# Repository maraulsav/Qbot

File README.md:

# Qbot-the-self-balancing-robot
Qbot is a self balancing robot that integrate PID mechanism to balances.

The Final Design:

## Key Features
* **ESP32 DevKit C** is the main microcontroller allowing wifi connection for remote controller
* **OLED display 128 x 64 px** for displaying the faces and current state of emotion
* **15 V Lipo Battery** to give power supply
* **MPU 6050** Act as gyroscope and accelerator to measure the degree of robot imbalance
* **Buzzer** to make sounds
* **Button** to regulate the power supply from battery
* **DC DC Buck Converter** to regulate the voltage supply
* **TMC2208 Motor Driver** To help control the wheel motion

## Printed Circuit Board (PCB)
Below is the schematic that I used

Below is the PCB design

And here how to connect the PCB to other component of the robot

**PCB Footprint List**
* 10uF capacitor: Capacitor_THT:CP_Radial_D5.0mm_P2.00mm
* 100uF capacitor: Capacitor_THT:CP_Radial_D6.3mm_P2.50mm
* Zener Diode: Diode_THT:D_DO-35_SOD27_P10.16mm_Horizontal
* LED: LED_THT:LED_D3.0mm
* Mounting Hole: MountingHole:MountingHole_3.2mm_M3
* Connector: Connector_PinHeader_2.54mm:PinHeader_1x04_P2.54mm_Vertical
* Connector 1x02: Connector_AMASS:AMASS_XT30U-M_1x02_P5.0mm_Vertical
* GY521 (MPU6050): GY-521:MODULE_GY-521
* ESP32 DevKit C: Library:MODULE_ESP32-DEVKITC
* TMC2208_SILENTSTEPSTICK:MODULE_TMC2208_SILENTSTEPSTICK

## 3D Design
Note that I would be using 12 cm wheel

Front Side

Right Side

Back Side

## Codes
Code Sample:

## BOM
| Component | Qty | Total (IDR) | Total (USD) | Link |
|-----------|----:|------------:|------------:|------|
| Stepper Motor 17HS4401S | 2 | - | $19.08 |[Link](https://www.aliexpress.com/item/1005008098470320.html?spm=a2g0o.productlist.main.2.28cfa8cpa8cpOK&algo_pvid=d640442b-15d3-4dfb-b6e0-f32e19ed61e5&algo_exp_id=d640442b-15d3-4dfb-b6e0-f32e19ed61e5-1&pdp_ext_f=%7B%22order%22%3A%2252%22%2C%22spu_best_type%22%3A%22price%22%2C%22eval%22%3A%221%22%2C%22fromPage%22%3A%22search%22%7D&pdp_npi=6%40dis%21SGD%219.54%215.26%21%21%217.26%214.00%21%400be71e1e17897422834053183e0cf3%2112000043729379107%21sea%21SG%210%21ABX%211%210%21n_tag%3A-29910%3Bd%3A420eb142%3Bm03_new_user%3A-29895%3BpisId%3A5000000216897878&curPageLogUid=qqeqjQQUr7C6&utparam-url=scene%3Asearch%7Cquery_from%3A%7Cx_object_id%3A1005008098470320%7C_p_origin_prod%3A) |
| Printed Circuit Board (PCB) | 1 | — | $3.50 | — |
| 2 x Metal 1.9 Beadlock Wheel Rim | 1 | - | $11.12 | [Link](https://www.aliexpress.com/item/1005007014668118.html?spm=a2g0o.detail.pcDetailTopMoreOtherSeller.7.5bc38Zkk8ZkkT0&gps-id=pcDetailTopMoreOtherSeller&scm=1007.40050.354490.0&scm_id=1007.40050.354490.0&scm-url=1007.40050.354490.0&pvid=f04b389a-01f7-4b2c-ba6d-c70562b40c5f&_t=gps-id%3ApcDetailTopMoreOtherSeller%2Cscm-url%3A1007.40050.354490.0%2Cpvid%3Af04b389a-01f7-4b2c-ba6d-c70562b40c5f%2Ctpp_buckets%3A668%232846%238107%231934&pdp_ext_f=%7B%22order%22%3A%222117%22%2C%22eval%22%3A%221%22%2C%22orig_sl_item_id%22%3A%221005007014668118%22%2C%22orig_item_id%22%3A%221005006293262517%22%2C%22sceneId%22%3A%2230050%22%2C%22fromPage%22%3A%22recommend%22%7D&pdp_npi=6%40dis%21SGD%2153.40%2121.16%21%21%21272.16%21107.84%21%402101364a17897780030878767e0dea%2112000039073751961%21rec%21SG%21%21ABXZ%211%210%21n_tag%3A-29910%3Bd%3A420eb142%3Bm03_new_user%3A-29895%3BpisId%3A5000000216897878&utparam-url=scene%3ApcDetailTopMoreOtherSeller%7Cquery_from%3A%7Cx_object_id%3A1005007014668118%7C_p_origin_prod%3A1005006293262517) |
| 4pcs 1.9" Wheel Tires (120mm) | 1 | 85,000 | $4.73 | [Link](https://www.aliexpress.com/item/1005005554788142.html?spm=a2g0o.detail.pcDetailTopMoreOtherSeller.1.158bpcuTpcuTd8&gps-id=pcDetailTopMoreOtherSeller&scm=1007.40050.354490.0&scm_id=1007.40050.354490.0&scm-url=1007.40050.354490.0&pvid=8bba8d91-1173-41c4-b8f4-5bd03e205a5a&_t=gps-id%3ApcDetailTopMoreOtherSeller%2Cscm-url%3A1007.40050.354490.0%2Cpvid%3A8bba8d91-1173-41c4-b8f4-5bd03e205a5a%2Ctpp_buckets%3A668%232846%238114%231999&pdp_ext_f=%7B%22order%22%3A%22644%22%2C%22spu_best_type%22%3A%22price%22%2C%22eval%22%3A%221%22%2C%22sceneId%22%3A%2230050%22%2C%22fromPage%22%3A%22recommend%22%7D&pdp_npi=6%40dis%21SGD%2144.13%2111.07%21%21%21224.90%2156.39%21%402101364a17897780992413207e0dea%2112000033522268566%21rec%21SG%21%21ABXZ%211%210%21n_tag%3A-29910%3Bd%3A420eb142%3Bm03_new_user%3A-29895%3BpisId%3A5000000216897878&utparam-url=scene%3ApcDetailTopMoreOtherSeller%7Cquery_from%3A%7Cx_object_id%3A1005005554788142%7C_p_origin_prod%3A) |
| ESP32-C3 DevKit | 1 | 85,000 | $4.73 | [Link](https://www.tokopedia.com/temins/esp32-nodemcu-esp-32-esp32s-32s-wifi-module-devkit-dev-38-pin-1729797014153692567?t_id=1782901083899&t_st=27&t_pp=cart&t_efo=cart&t_ef=&t_sm=&t_spt=cart) |
| GY-521 MPU-6050 | 1 | 29,500 | $1.64 | [Link](https://www.tokopedia.com/khurs-iot/gy-521-mpu-6050-3-axis-accelerometer-gyroscope-arduino-raspberry-pi?extParam=ivf%3Dfalse%26keyword%3Dgy-521+module+with+mpu-6050%26search_id%3D20260703094308371BCE7DC8381718578F%26src%3Dsearch&t_id=1782901083899&t_st=24&t_pp=search_result&t_efo=search_pure_goods_card&t_ef=goods_search&t_sm=&t_spt=search_result) |
| TMC2208 Motor Driver | 2 | - | $5,82 | [Link](https://www.aliexpress.com/item/1005010480173953.html?spm=a2g0o.productlist.main.8.125354a13eYaZq&aem_p4p_detail=202609181704121512827017702700000065849&algo_pvid=482b89e2-b950-42ca-bd5d-87d05453ec1d&algo_exp_id=482b89e2-b950-42ca-bd5d-87d05453ec1d-7&pdp_ext_f=%7B%22order%22%3A%22294%22%2C%22eval%22%3A%221%22%2C%22fromPage%22%3A%22search%22%7D&pdp_npi=6%40dis%21SGD%2116.38%213.10%21%21%2183.47%2115.81%21%402101737817897762521998069e0f37%2112000052545395846%21sea%21SG%210%21ABX%211%210%21n_tag%3A-29910%3Bd%3A420eb142%3Bm03_new_user%3A-29895%3BpisId%3A5000000216897878&curPageLogUid=mdaYc0tmK80y&utparam-url=scene%3Asearch%7Cquery_from%3A%7Cx_object_id%3A1005010480173953%7C_p_origin_prod%3A&search_p4p_id=202609181704121512827017702700000065849_2) |
| LiPo Battery (11.1V) | 1 | 169,200 | $9.42 | [Link](https://www.tokopedia.com/rin-toys/baterai-lipo-11-1-volt-3s-batre-lithium-polymer-for-wgg-mobil-rc-1734386815592072921?extParam=ivf%3Dfalse%26keyword%3Dlipobattery%26search_id%3D20260703100056B83AAC23B952872AFVWB%26src%3Dsearch&t_id=1782901083899&t_st=34&t_pp=search_result&t_efo=search_pure_goods_card&t_ef=goods_search&t_sm=&t_spt=search_result) |
| LiPo Battery Charger | 1 | 65,000 | $3.61 | [Link](https://www.tokopedia.com/rin-toys/charger-baterai-balance-charger-for-2s-3s-7-4v-11-1v-lithium-lipo-battery-1731018524016871129?extParam=whid%3D18463153%26src%3Dchat) |
| Neodymium Magnet | 1 | 20,000 | $1.11 | [Link](https://www.tokopedia.com/tokodstore/magnet-kuat-neodymium-bulat-diy-5-3mm-50pcs?extParam=ivf%3Dfalse%26keyword%3Dmini+magnet%26search_id%3D202607050039293FE94A002317B5346ZJK%26src%3Dsearch&t_id=1783211974588&t_st=1&t_pp=search_result&t_efo=search_pure_goods_card&t_ef=goods_search&t_sm=&t_spt=search_result) |
| OLED Display | 2 | 73,000 | $4.09 | [Link](https://www.tokopedia.com/cncstorebandung/oled-display-0-96-inch-i2c-128-64-layar-oled-putih-biru-kuning-biru-untuk-arduino-esp32-dan-proyek-diy-1733644920011851326?extParam=ivf%3Dfalse%26keyword%3Doled+display+128+x+64%26search_id%3D202609181451126FAA8040DA20EF3A7R2E%26src%3Dsearch&t_id=1789743089846&t_st=1&t_pp=search_result&t_efo=search_pure_goods_card&t_ef=goods_search&t_sm=&t_spt=search_result)|
| Push Button | 1 | 15,000 | $0.83 | [Link](https://www.tokopedia.com/arduinonano/r16-503bd-4-pin-16mm-push-on-non-locked-button-switch-250v-light-merah?extParam=src%3Dshop%26whid%3D2850960&aff_unique_id=&channel=others&chain_key=) |
| Jumper Wire (15 cm, 40 pcs) | 1 pack | 23,000 | $1.28 | [Link](https://www.tokopedia.com/arduinonano/kabel-jumper-40p-cable-dupont-pelangi-15cm-40pin-header-cable-pin-rainbow-15-cm-1729801397622441069?extParam=src%3Dshop%26whid%3D2850960&aff_unique_id=&channel=others&chain_key=) |
| Header Pin | 1 pack | 14,000 | $0.78 | [Link](https://www.tokopedia.com/arduinonano/1x40-pin-2-0mm-male-single-row-header-strip-40-40p-pit-2mm-tulang-ikan?extParam=src%3Dshop%26whid%3D2850960&aff_unique_id=&channel=others&chain_key=) |
| Heatsink | 2 | 4,656 | $0.26 | [Link](https://www.tokopedia.com/rajacell/heatsink-aluminium-pendingin-14x14x6mm-dengan-3m-thermal-tape?extParam=ivf%3Dfalse%26keyword%3Dheat+set+insert+%26search_id%3D202607080016323FE94A002317B501AGHP%26src%3Dsearch&t_id=1783310432964&t_st=4&t_pp=search_result&t_efo=search_pure_goods_card&t_ef=goods_search&t_sm=&t_spt=search_result) |
| Heat-Set Inserts | 1 | 252,200 | $14.02 | [Link](https://www.tokopedia.com/smbility/insert-nut-kuningan-hot-500pcs-hot-melt-nutinsert-thread-knurled-spiral-brass-nut-insert-1730606018733835796?extParam=ivf%3Dfalse%26keyword%3Dheat+insert+m3%26search_id%3D20260708002015C042F4DB68F234374NW5%26src%3Dsearch&t_id=1783310432964&t_st=8&t_pp=search_result&t_efo=search_pure_goods_card&t_ef=goods_search&t_sm=&t_spt=search_result) |
| Nut Set | 1 | 131,000 | $7.28 | [Link](https://www.tokopedia.com/fyn-by-finedego/baut-set-m3-m4-m5-m6-600-pcs-hex-ring-mur-screw-bolt-nuts-assortment-kit-stainless-steel-l-bulat-40mm-30mm-20mm-10mm-16mm-12mm-8mm-paket-taffware-sa6-1734446427248887202?extParam=ivf%3Dfalse%26keyword%3Dheat+insert+nut+m3+x+4mm%26search_id%3D20260708002226AD972F10E0800B042LX3%26src%3Dsearch&t_id=1783310432964&t_st=9&t_pp=search_result&t_efo=search_pure_goods_card&t_ef=goods_search&t_sm=&t_spt=search_result) |
| 10 µF Capacitor | 1 | 20,400 | $1.14 | [Link](https://www.tokopedia.com/lektropedia/elco-10uf-450v-kapasitor-10-uf-mikro-450-v-volt-elko-450volt-capasitor-1-49-pcs-ed5a8?extParam=ivf%3Dfalse%26keyword%3Dcapacitor+10uf%26search_id%3D20260708004347A49E9411D64FF5084HN8%26src%3Dsearch&t_id=1783310432964&t_st=10&t_pp=search_result&t_efo=search_pure_goods_card&t_ef=goods_search&t_sm=&t_spt=search_result) |
| 100 µF Capacitor | 3 | 24,900 | $1.16 | [Link](https://www.tokopedia.com/lektropedia/elco-100uf-450v-kapasitor-100-uf-mikro-450-v-volt-elko-450volt?extParam=ivf%3Dfalse%26keyword%3Dcapacitor+100+uf%26search_id%3D2026070800445800EC53C4682D362CDQEE%26src%3Dsearch&t_id=1783310432964&t_st=11&t_pp=search_result&t_efo=search_pure_goods_card&t_ef=goods_search&t_sm=&t_spt=search_result) |
| Zener Diode | 1 | 10,000 | $0.56 | [Link](https://www.tokopedia.com/arduinonano/dioda-zener-1w-3v6-3-6v-1n4729a-in4729a-1n4729-in4729-diode-do-41?extParam=ivf%3Dfalse%26keyword%3Dzener+diode%26search_id%3D2026070800473015D4E891D7849731AFTY%26src%3Dsearch&t_id=1783310432964&t_st=12&t_pp=search_result&t_efo=search_pure_goods_card&t_ef=goods_search&t_sm=&t_spt=search_result) |
| LED | 1 | 1,250 | $0.07 | [Link](https://www.tokopedia.com/arduinonano/led-blink-red-5mm-diode-super-bright-led-kedip-merah-led-5mm-kedip?extParam=src%3Dshop%26whid%3D2850960&aff_unique_id=&channel=others&chain_key=) |
| 1 kΩ Resistor | 1 | 15,000 | $0.83 | [Link](https://www.tokopedia.com/arduinonano/10pcs-resistor-1k-1-kilo-k-ohm-1-4-watt-0-25-metal-film-tolerance-1?extParam=ivf%3Dfalse%26keyword%3D1k+resistor%26search_id%3D202607080049581543843A4723ED160GND%26src%3Dsearch&t_id=1783310432964&t_st=15&t_pp=search_result&t_efo=search_pure_goods_card&t_ef=goods_search&t_sm=&t_spt=search_result) |
| LM2596S  DC to DC Buck Converter | 1 | 34,200 | $1,92 | [Link](https://www.tokopedia.com/tokoasia-jkt/lm2596s-buck-converter-dc-dc-step-down-voltage-regulator-36v-24v-12v-to-5v-2a-volt-digital-display-2596s-1730718483558664143?extParam=ivf%3Dfalse%26keyword%3Dbuck+converter%26search_id%3D20260810013330A96B65A721E5611F1YFR%26src%3Dsearch&t_id=1786325702593&t_st=3&t_pp=search_result&t_efo=search_pure_goods_card&t_ef=goods_search&t_sm=&t_spt=search_result) |
| Active Buzzer | 1 | 5,000 | $0.28 | [Link](https://www.tokopedia.com/azzamarduino/buzzer-speaker-aktif-active-dc-3v-24v-sfm-27-3cm-input-3v-5v-12v-bunyi?extParam=ivf%3Dfalse%26keyword%3Dbuzzer%26search_id%3D20260708005325CD00692C3BFE5926FWW3%26src%3Dsearch&t_id=1783310432964&t_st=17&t_pp=search_result&t_efo=search_pure_goods_card&t_ef=goods_search&t_sm=&t_spt=search_result) |
| XT30 Amass Connector | 1 | 8,500 | $0.47 | [Link](https://www.tokopedia.com/arduinonano/amass-connector-plug-xt30u-amass-xt-30-u-konektor-for-power-1732555087363605613?extParam=ivf%3Dfalse%26keyword%3Damass+connector%26search_id%3D202607080057278BF1211FD4B7B91A5G6M%26src%3Dsearch&t_id=1783310432964&t_st=19&t_pp=search_result&t_efo=search_pure_goods_card&t_ef=goods_search&t_sm=&t_spt=search_result) |
| 3D Printed Parts | — | — | $9.00 | — |
| **Total** | | **IDR2.049.638** | **USD 115.07** | |

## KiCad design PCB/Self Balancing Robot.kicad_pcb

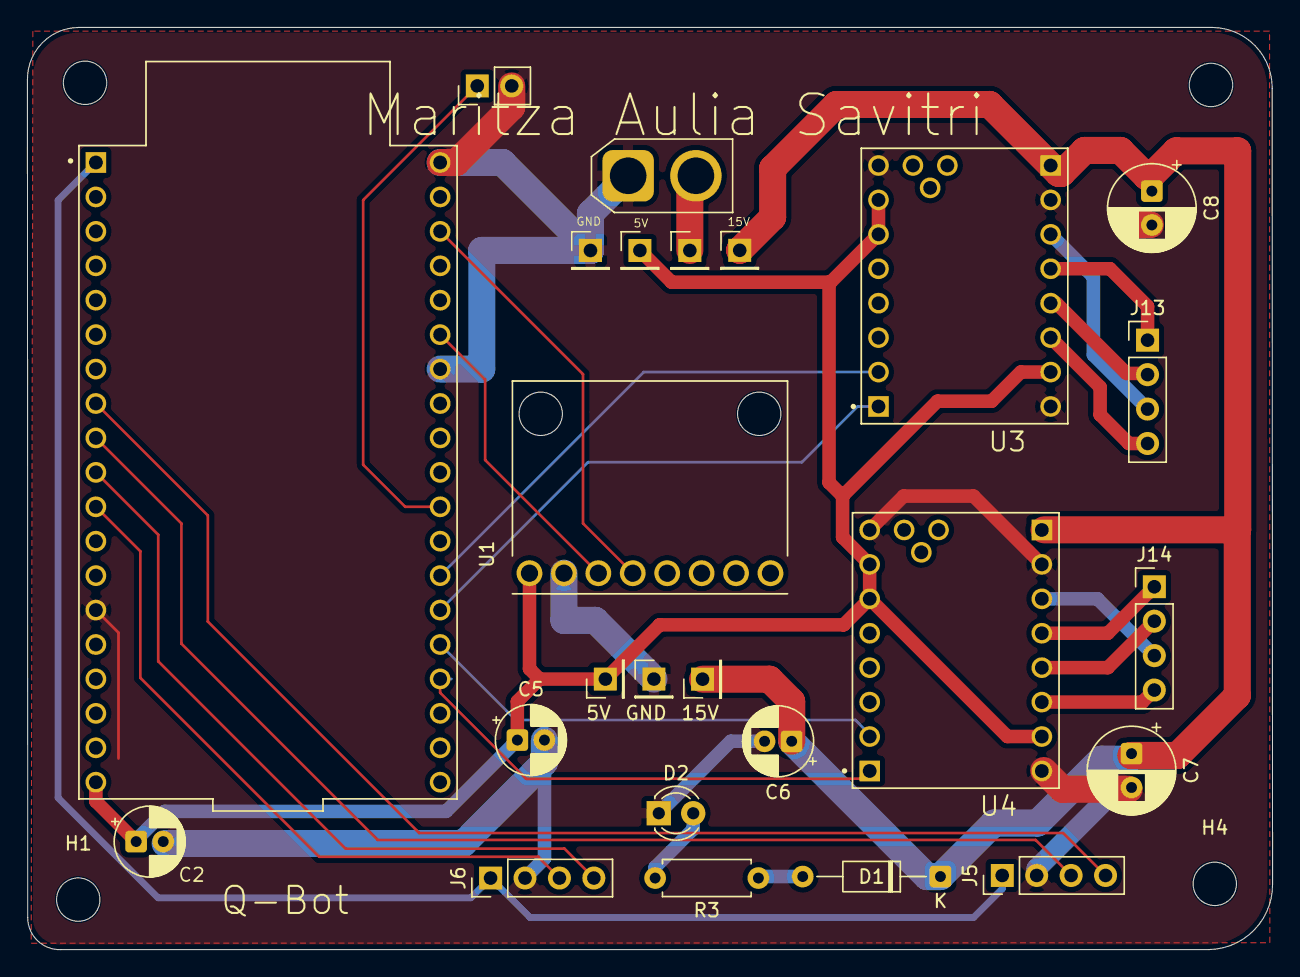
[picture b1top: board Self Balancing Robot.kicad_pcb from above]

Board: 2 copper layers, 91.9 x 68.0 mm, 29 parts (0 on the bottom side), 26 nets.

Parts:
5V, 15V: Conn_01x01; PinHeader_1x01_P2.54mm_Vertical
C2, C5, C6: 10uF; CP_Radial_D5.0mm_P2.00mm
C7, C8: 100uF; CP_Radial_D6.3mm_P2.50mm
D1: D_Zener; D_DO-35_SOD27_P10.16mm_Horizontal
D2: LED; LED_D3.0mm
GND: Conn_01x01; PinHeader_1x01_P2.54mm_Vertical
H1, H2, H3, H4: MountingHole; MountingHole_3.2mm_M3
J3: Conn_01x02; AMASS_XT30U-M_1x02_P5.0mm_Vertical
J4: -SW; PinHeader_1x01_P2.54mm_Vertical
J5, J6, J13, J14: Conn_01x04; PinHeader_1x04_P2.54mm_Vertical
J7: +SW; PinHeader_1x01_P2.54mm_Vertical
J8: +SWLED; PinHeader_1x01_P2.54mm_Vertical
J9: -SWLED; PinHeader_1x01_P2.54mm_Vertical
J10: Conn_01x02; PinHeader_1x02_P2.54mm_Vertical
R3: 1k; R_Axial_DIN0207_L6.3mm_D2.5mm_P7.62mm_Horizontal
U1: GY-521; MODULE_GY-521
U2: ESP32-DEVKITC; MODULE_ESP32-DEVKITC
U3, U4: TMC2208_SILENTSTEPSTICK; MODULE_TMC2208_SILENTSTEPSTICK

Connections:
+3V3: J5.1, J6.1, U2.1 (3V3)
+5V: 5V.1 (Pin_1_1), C2.1, C5.1, J8.1 (Pin_1_1), U1.VCC, U2.19 (EXT_5V), U3.JP1_6 (MS2), U3.JP1_7 (MS1), U3.JP2_7 (VIO), U4.JP1_6 (MS2), U4.JP1_7 (MS1), U4.JP2_7 (VIO)
+15V: 15V.1 (Pin_1_1), C6.1, C7.1, C8.1, D1.1 (K), J7.1 (Pin_1_1), U3.JP2_1 (VM), U4.JP2_1 (VM)
/IO17: J10.1, U2.28 (IO17)
/MDDIR1: U2.25 (IO0), U3.JP1_1 (DIR)
/MDDIR2: U2.23 (IO15), U4.JP1_1 (DIR)
/MDSTEP1: U2.26 (IO4), U3.JP1_2 (STEP)
/MDSTEP2: U2.24 (IO2), U4.JP1_2 (STEP)
/SCL: U1.SDA, U2.36 (IO22)
/SCL1: J5.3, U2.9 (IO25)
/SCL2: J6.3, U2.11 (IO27)
/SDA: U1.SCL, U2.33 (IO21)
/SDA1: J5.4, U2.8 (IO33)
/SDA2: J6.4, U2.10 (IO26)
GND: C2.2, C5.2, C6.2, C7.2, C8.2, D2.1 (K), GND.1 (Pin_1_1), J3.1, J5.2, J6.2, J9.1 (Pin_1_1), J10.2, U1.GND, U2.14 (GND1), U2.32 (GND2), U2.38 (GND3), U3.JP1_8 (EN), U3.JP2_2 (GND), U3.JP2_8 (GND), U4.JP1_8 (EN), U4.JP2_2 (GND), U4.JP2_8 (GND)
unnamed: D1.2 (A), R3.1
unnamed: D2.2 (A), R3.2
unnamed: J3.2, J4.1 (Pin_1_1)
unnamed: J13.1, U3.JP2_4 (OA1)
unnamed: J13.2, U3.JP2_5 (OB1)
unnamed: J13.3, U3.JP2_3 (OA2)
unnamed: J13.4, U3.JP2_6 (OB2)
unnamed: J14.1, U4.JP2_4 (OA1)
unnamed: J14.2, U4.JP2_5 (OB1)
unnamed: J14.3, U4.JP2_3 (OA2)
unnamed: J14.4, U4.JP2_6 (OB2)
